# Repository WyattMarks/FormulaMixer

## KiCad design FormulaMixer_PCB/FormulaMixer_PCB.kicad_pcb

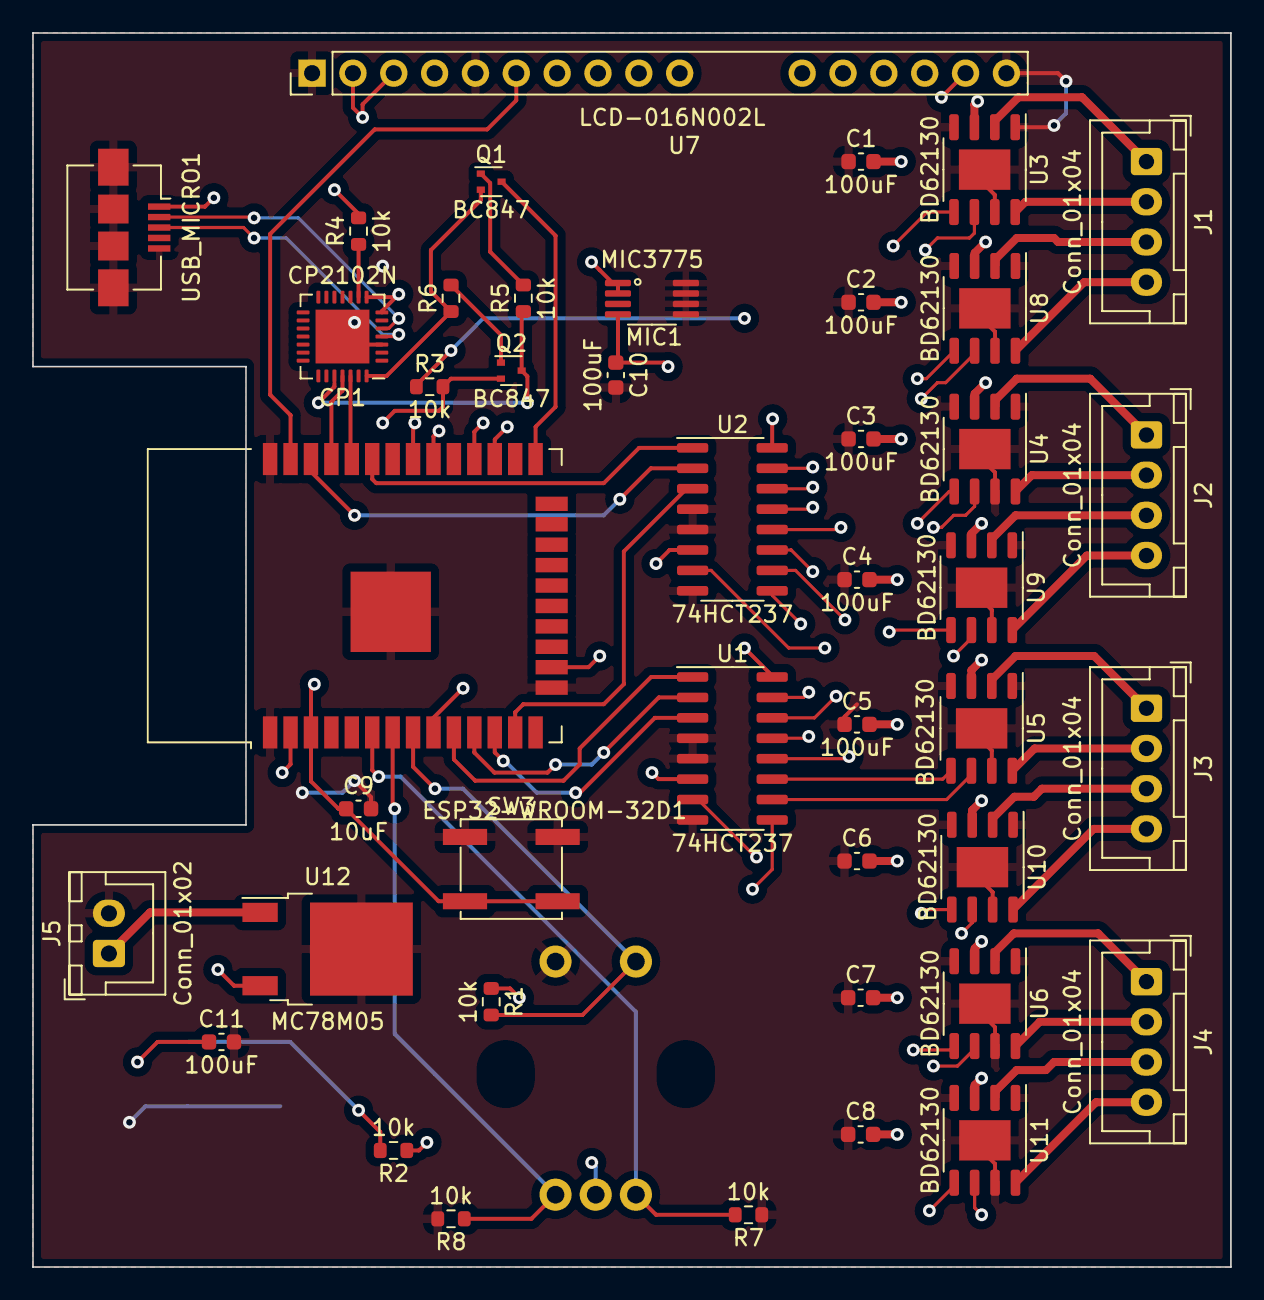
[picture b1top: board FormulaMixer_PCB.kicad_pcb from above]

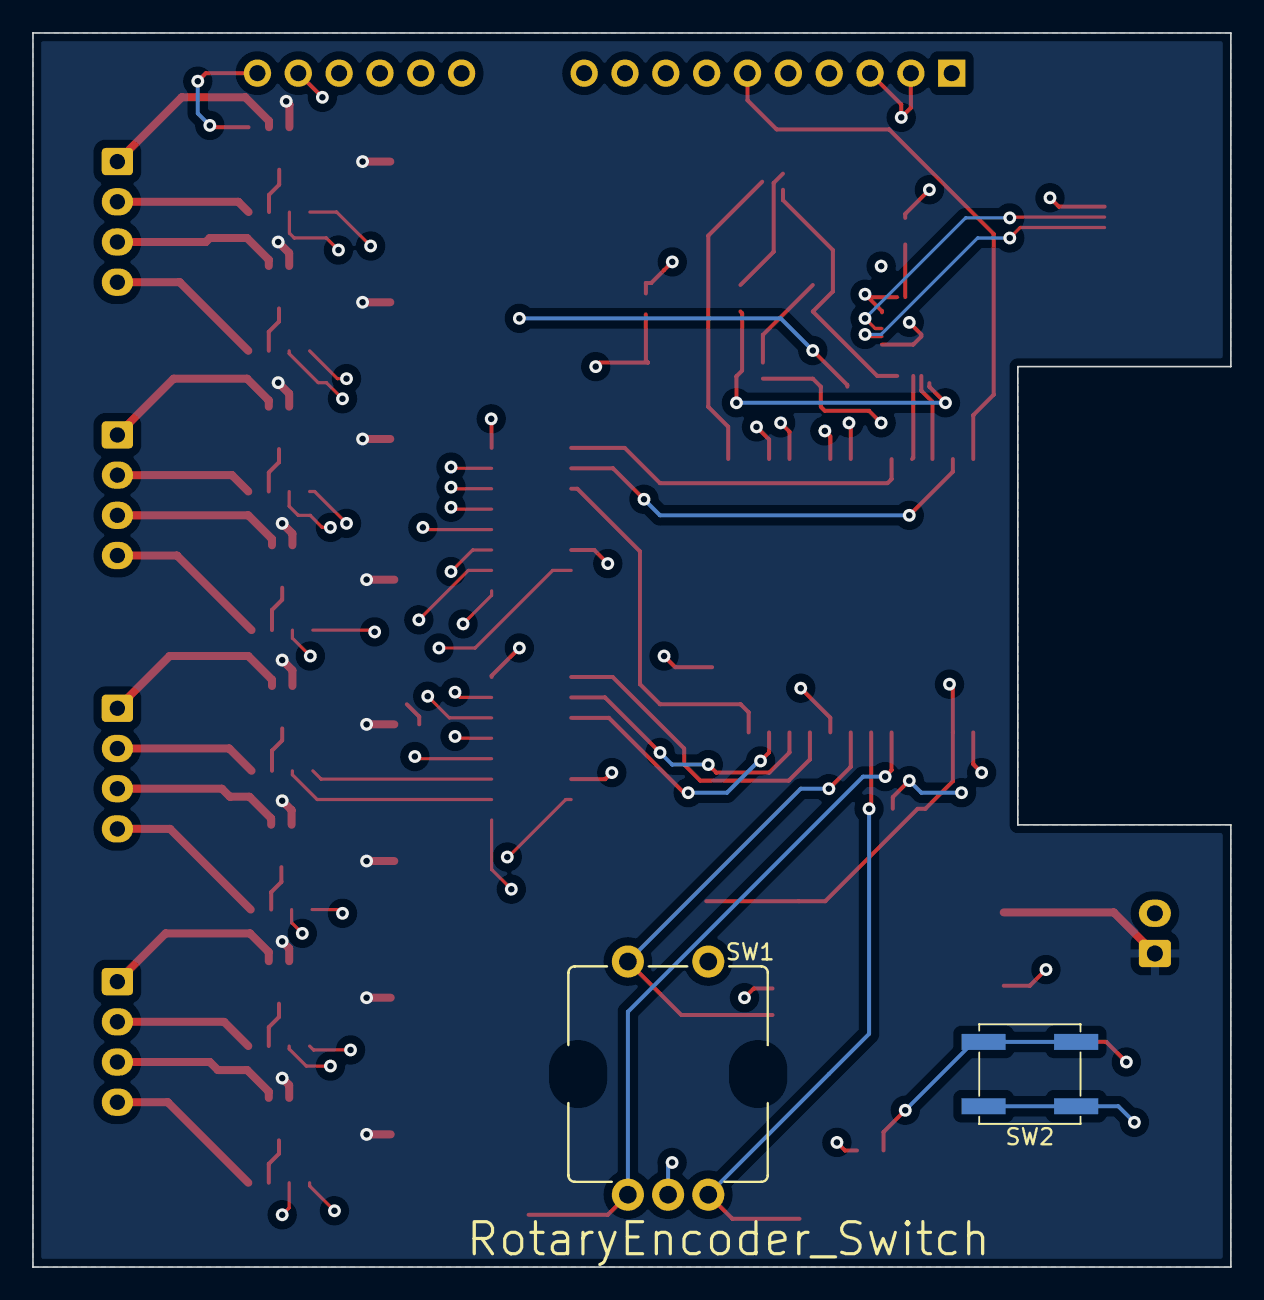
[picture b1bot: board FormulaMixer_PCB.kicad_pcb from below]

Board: 4 copper layers, 74.5 x 76.8 mm, 45 parts (2 on the bottom side), 63 nets.

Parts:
C1, C2, C3, C4, C5, C6, C7, C8, C10, C11: 100uF; C_0603_1608Metric
C9: 10uF; C_0603_1608Metric
CP1: CP2102N; QFN-28-1EP_5x5mm_P0.5mm_EP3.35x3.35mm
ESP32-WROOM-32D1: ESP32-WROOM-32D; ESP32-WROOM-32
J1, J2, J3, J4: Conn_01x04; JST_XH_B4B-XH-A_1x04_P2.50mm_Vertical
J5: Conn_01x02; JST_XH_B2B-XH-A_1x02_P2.50mm_Vertical
MIC1: MIC3775; MSOP8-Reg
Q1, Q2: BC847; SOT-523
R1, R2, R3, R4, R5, R6, R7, R8: 10k; R_0603_1608Metric
SW1: RotaryEncoder_Switch; PEC12R-4xxF-Sxxxx
SW2, SW3: SW_Push; SW_SPST_EVPBF
U1, U2: 74HCT237; SOIC-16_3.9x9.9mm_P1.27mm
U3, U4, U5, U6, U8, U9, U10, U11: BD62130; SOIC-8-1EP_3.9x4.9mm_P1.27mm_EP2.514x3.2mm
U7: LCD-016N002L; LCD_HEADER
U12: MC78M05; TO-252-2
USB_MICRO1: USB_B_Micro; USB_Micro-B_Amphenol_10104110_Horizontal

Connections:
+3V3: C10.1, ESP32-WROOM-32D1.2 (VDD), MIC1.OUT, R1.1, R2.1, R3.1, SW1.C, U1.6 (E2), U1.16 (VCC), U2.6 (E2), U2.16 (VCC)
+5V: C11.1, CP1.7 (VREGIN), CP1.8 (VBUS), MIC1.EN, MIC1.IN, R4.2, U7.2 (VDD), U7.3 (VO), U7.15 (A/VEE), U12.3 (VO), USB_MICRO1.1 (VBUS)
+12V: C1.2, C2.2, C3.2, C4.2, C5.2, C6.2, C7.2, C8.2, J5.1, U3.3 (Vcc), U4.3 (Vcc), U5.3 (Vcc), U6.3 (Vcc), U8.3 (Vcc), U9.3 (Vcc), U10.3 (Vcc), U11.3 (Vcc), U12.1 (VI)
/BTN: ESP32-WROOM-32D1.9 (IO33), R2.2, SW2.2
/D+: CP1.4 (D+), USB_MICRO1.3 (D+)
/D-: CP1.5 (D-), USB_MICRO1.2 (D-)
/DB4: ESP32-WROOM-32D1.30 (IO18), U7.11 (DB4)
/DB5: ESP32-WROOM-32D1.28 (IO17), U7.12 (DB5)
/DB6: ESP32-WROOM-32D1.27 (IO16), U7.13 (DB6)
/DB7: ESP32-WROOM-32D1.16 (IO13), U7.14 (DB7)
/DTR: CP1.28 (~DTR), Q1.2 (E), R6.1
/E: ESP32-WROOM-32D1.37 (IO23), U7.6 (E)
/ENC_A: ESP32-WROOM-32D1.6 (IO34), R7.2, SW1.A
/ENC_B: ESP32-WROOM-32D1.7 (IO35), R8.1, SW1.B
/ENC_BTN: ESP32-WROOM-32D1.8 (IO32), R1.2, SW1.S1
/GPIO0: ESP32-WROOM-32D1.25 (IO0), Q1.3 (C)
/M1_1N: J1.2, U3.8 (OUT2)
/M1_1P: J1.1, U3.2 (OUT1)
/M1_2N: J1.4, U8.8 (OUT2)
/M1_2P: J1.3, U8.2 (OUT1)
/M2_1N: J2.2, U4.8 (OUT2)
/M2_1P: J2.1, U4.2 (OUT1)
/M2_2N: J2.4, U9.8 (OUT2)
/M2_2P: J2.3, U9.2 (OUT1)
/M3_1N: J3.2, U5.8 (OUT2)
/M3_1P: J3.1, U5.2 (OUT1)
/M3_2N: J3.4, U10.8 (OUT2)
/M3_2P: J3.3, U10.2 (OUT1)
/M4_1N: J4.2, U6.8 (OUT2)
/M4_1P: J4.1, U6.2 (OUT1)
/M4_2N: J4.4, U11.8 (OUT2)
/M4_2P: J4.3, U11.2 (OUT1)
/P1M1_N: U1.14 (Y1), U3.6 (IN2)
/P1M1_P: U1.15 (Y0), U3.5 (IN1)
/P1M2_N: U1.12 (Y3), U4.6 (IN2)
/P1M2_P: U1.13 (Y2), U4.5 (IN1)
/P1M3_N: U1.10 (Y5), U5.6 (IN2)
/P1M3_P: U1.11 (Y4), U5.5 (IN1)
/P1M4_N: U1.7 (Y7), U6.6 (IN2)
/P1M4_P: U1.9 (Y6), U6.5 (IN1)
/P2M1_N: U2.14 (Y1), U8.6 (IN2)
/P2M1_P: U2.15 (Y0), U8.5 (IN1)
/P2M2_N: U2.12 (Y3), U9.6 (IN2)
/P2M2_P: U2.13 (Y2), U9.5 (IN1)
/P2M3_N: U2.10 (Y5), U10.6 (IN2)
/P2M3_P: U2.11 (Y4), U10.5 (IN1)
/P2M4_N: U2.7 (Y7), U11.6 (IN2)
/P2M4_P: U2.9 (Y6), U11.5 (IN1)
/RESET: C9.1, ESP32-WROOM-32D1.3 (EN), Q2.2 (E), R3.2, SW3.2
/RS: ESP32-WROOM-32D1.31 (IO19), U7.4 (RS)
/RTS: CP1.24 (~RTS), Q2.3 (C), R5.1
/RX_ESP: CP1.26 (TXD), ESP32-WROOM-32D1.34 (RXD0/IO3)
/S0_P1: ESP32-WROOM-32D1.10 (IO25), U1.1 (A0)
/S0_P2: ESP32-WROOM-32D1.33 (IO21), U2.1 (A0)
/S1_P1: ESP32-WROOM-32D1.11 (IO26), U1.2 (A1)
/S1_P2: ESP32-WROOM-32D1.36 (IO22), U2.2 (A1)
/S2_P1: ESP32-WROOM-32D1.12 (IO27), U1.3 (A2)
/S2_P2: ESP32-WROOM-32D1.13 (IO14), U2.3 (A2)
/TX_ESP: CP1.25 (RXD), ESP32-WROOM-32D1.35 (TXD0/IO1)
GND: C1.1, C2.1, C3.1, C4.1, C5.1, C6.1, C7.1, C8.1, C9.2, C10.2, C11.2, CP1.3 (GND), CP1.29 (GND), ESP32-WROOM-32D1.1 (GND), ESP32-WROOM-32D1.15 (GND), ESP32-WROOM-32D1.38 (GND), ESP32-WROOM-32D1.39 (GND), J5.2, MIC1.GND, R7.1, R8.2, SW1.S2, SW2.1, SW3.1, U1.4 (~LE), U1.5 (~E1), U1.8 (GND), U2.4 (~LE), U2.5 (~E1), U2.8 (GND), U3.1 (GND), U3.4 (GND), U3.7 (Test), U3.9, U4.1 (GND), U4.4 (GND), U4.7 (Test), U4.9, U5.1 (GND), U5.4 (GND), U5.7 (Test), U5.9, U6.1 (GND), U6.4 (GND), U6.7 (Test), U6.9, U7.1 (VSS), U7.5 (R/~W), U7.16 (K), U8.1 (GND), U8.4 (GND), U8.7 (Test), U8.9, U9.1 (GND), U9.4 (GND), U9.7 (Test), U9.9, U10.1 (GND), U10.4 (GND), U10.7 (Test), U10.9, U11.1 (GND), U11.4 (GND), U11.7 (Test), U11.9, U12.2 (GND), USB_MICRO1.5 (GND), USB_MICRO1.6 (Shield)
unnamed: CP1.9 (~RST), R4.1
unnamed: Q1.1 (B), R5.2
unnamed: Q2.1 (B), R6.2

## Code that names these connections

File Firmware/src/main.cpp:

#include <Arduino.h>
#include <LiquidCrystal.h>
#include "GUI/GUI.h"
#include "Stepper/Stepper.h"
typedef void (*callbackFunction)(void);

#define ENC_A 34
#define ENC_B 35
#define SELECT 32
#define BACK 33


LiquidCrystal lcd(19, 23, 18, 17, 16, 13); //LCD Pins [ RS, EN, D4, D5, D6, D7 ]

Stepper motor1(0, 1);
Stepper motor2(2, 3);
Stepper motor3(4, 5);
Stepper motor4(6, 7);

void (*storage[10])();
String array[10];

callbackFunction main_menu_ptr;
callbackFunction menu_a_ptr;
callbackFunction menu_b_ptr;
callbackFunction stepper_ptr;
callbackFunction float_test_ptr;

uint8_t stepper_flag = 0;
uint8_t float_flag = 0;

void menu_a() {
	Vector<String> options;
	options.setStorage(array);
	options.push_back("Menu B");

	Vector<callbackFunction> callbacks;
	callbacks.setStorage(storage);
	callbacks.push_back(main_menu_ptr);
	callbacks.push_back(menu_b_ptr);

	GUI::createMenu(options, callbacks);
}

void menu_b() {
	Vector<String> options;
	options.setStorage(array);
	options.push_back("Menu A");

	Vector<callbackFunction> callbacks;
	callbacks.setStorage(storage);
	callbacks.push_back(main_menu_ptr);
	callbacks.push_back(menu_a_ptr);

	GUI::createMenu(options, callbacks);
}

void main_menu() {
	Vector<String> options;
	options.setStorage(array);
	options.push_back("Menu A");
	options.push_back("Menu B");
	options.push_back("Stepper Test");
	options.push_back("Float Test");

	
	Vector<callbackFunction> callbacks;
	callbacks.setStorage(storage);

	callbacks.push_back(main_menu_ptr);
	callbacks.push_back(menu_a_ptr);
	callbacks.push_back(menu_b_ptr);
	callbacks.push_back(stepper_ptr);
	callbacks.push_back(float_test_ptr);

	GUI::createMenu(options, callbacks);
}

void stepper() {
	lcd.clear();
	lcd.write("Trying to dispense..");
	GUI::disableInput();
	stepper_flag = 1;
}

void float_test() {
	lcd.clear();
	float_flag = 1;
}


void setup() {
	pinMode(ENC_A, INPUT);
	pinMode(ENC_B, INPUT);
	pinMode(SELECT, INPUT);
	pinMode(BACK, INPUT);

	pinMode(S0_P1, OUTPUT);
	pinMode(S1_P1, OUTPUT);
	pinMode(S2_P1, OUTPUT);
	pinMode(S0_P2, OUTPUT);
	pinMode(S1_P2, OUTPUT);
	pinMode(S2_P2, OUTPUT);
	pinMode(STEPPER_ENABLE, OUTPUT);

	digitalWrite(STEPPER_ENABLE, 0);

	Serial.begin(115200);
	lcd.begin(20, 4);
	lcd.clear();

	main_menu_ptr = main_menu;
	menu_a_ptr = menu_a;
	menu_b_ptr = menu_b;
	stepper_ptr = stepper;
	float_test_ptr = float_test;

	GUI::begin(&lcd);
	GUI::attachInterrupts(SELECT, BACK, ENC_A, ENC_B);

	main_menu();
}



void loop() {
	if (stepper_flag) {
		stepper_flag = 0;

		motor1.step(1000);
		delay(1000);
		motor1.step(-1000);

		motor2.step(1000);
		delay(1000);
		motor2.step(-1000);

		motor3.step(1000);
		delay(1000);
		motor3.step(-1000);

		motor4.step(1000);
		delay(1000);
		motor4.step(-1000);

		delay(1000);

		main_menu_ptr();
	}

	if (float_flag) {
		float_flag = 0;
		double test = GUI::getDouble("Test", 0.25);

		Serial.println( String(test).c_str() );

		String tester = GUI::getString("String", 5);

		Serial.println( tester.c_str() );

		main_menu_ptr();
	}

	usleep(5000);
}

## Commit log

2022-07-17 Initial idea
2022-07-17 Add initial PCB with nothing but the microcontroller and related components
2022-07-17 Remove KiCad's automatic backups from the git tree
2022-07-18 Add LCD and inputs to schematic
2022-07-18 Finalize BOM
2022-07-18 Add unsaved progress
2022-07-19 Add Demuxes and H-Bridges to schematic
2022-07-19 Add connectors to schematic
2022-07-19 Finish Schematic
2022-07-19 Assign all footprints
2022-07-22 Add external pullups to encoder output
2022-07-22 Ope those are suppose to be pulldowns
2022-07-22 Layout board
2022-07-22 Route PCB, melt PCB
2022-07-22 Annotate PCB some, add mounting holes
2022-07-22 Fix some silkscreen stuff
2022-08-17 Create basic menu system to use later
2022-08-17 Remove unused member variables
2022-08-17 Fix inputs being pulled up
2022-08-17 Create basic menu system to test with
2022-08-17 Oops, actually fix pullup inputs
2022-08-28 Make GUI use interrupts, get board running
2022-08-29 Create Stepper library for this board's setup (demuxes)
2022-09-01 Add a float input method (actually double because lack of float support in ISRs on ESP
2022-09-01 Make a method for inputting strings
